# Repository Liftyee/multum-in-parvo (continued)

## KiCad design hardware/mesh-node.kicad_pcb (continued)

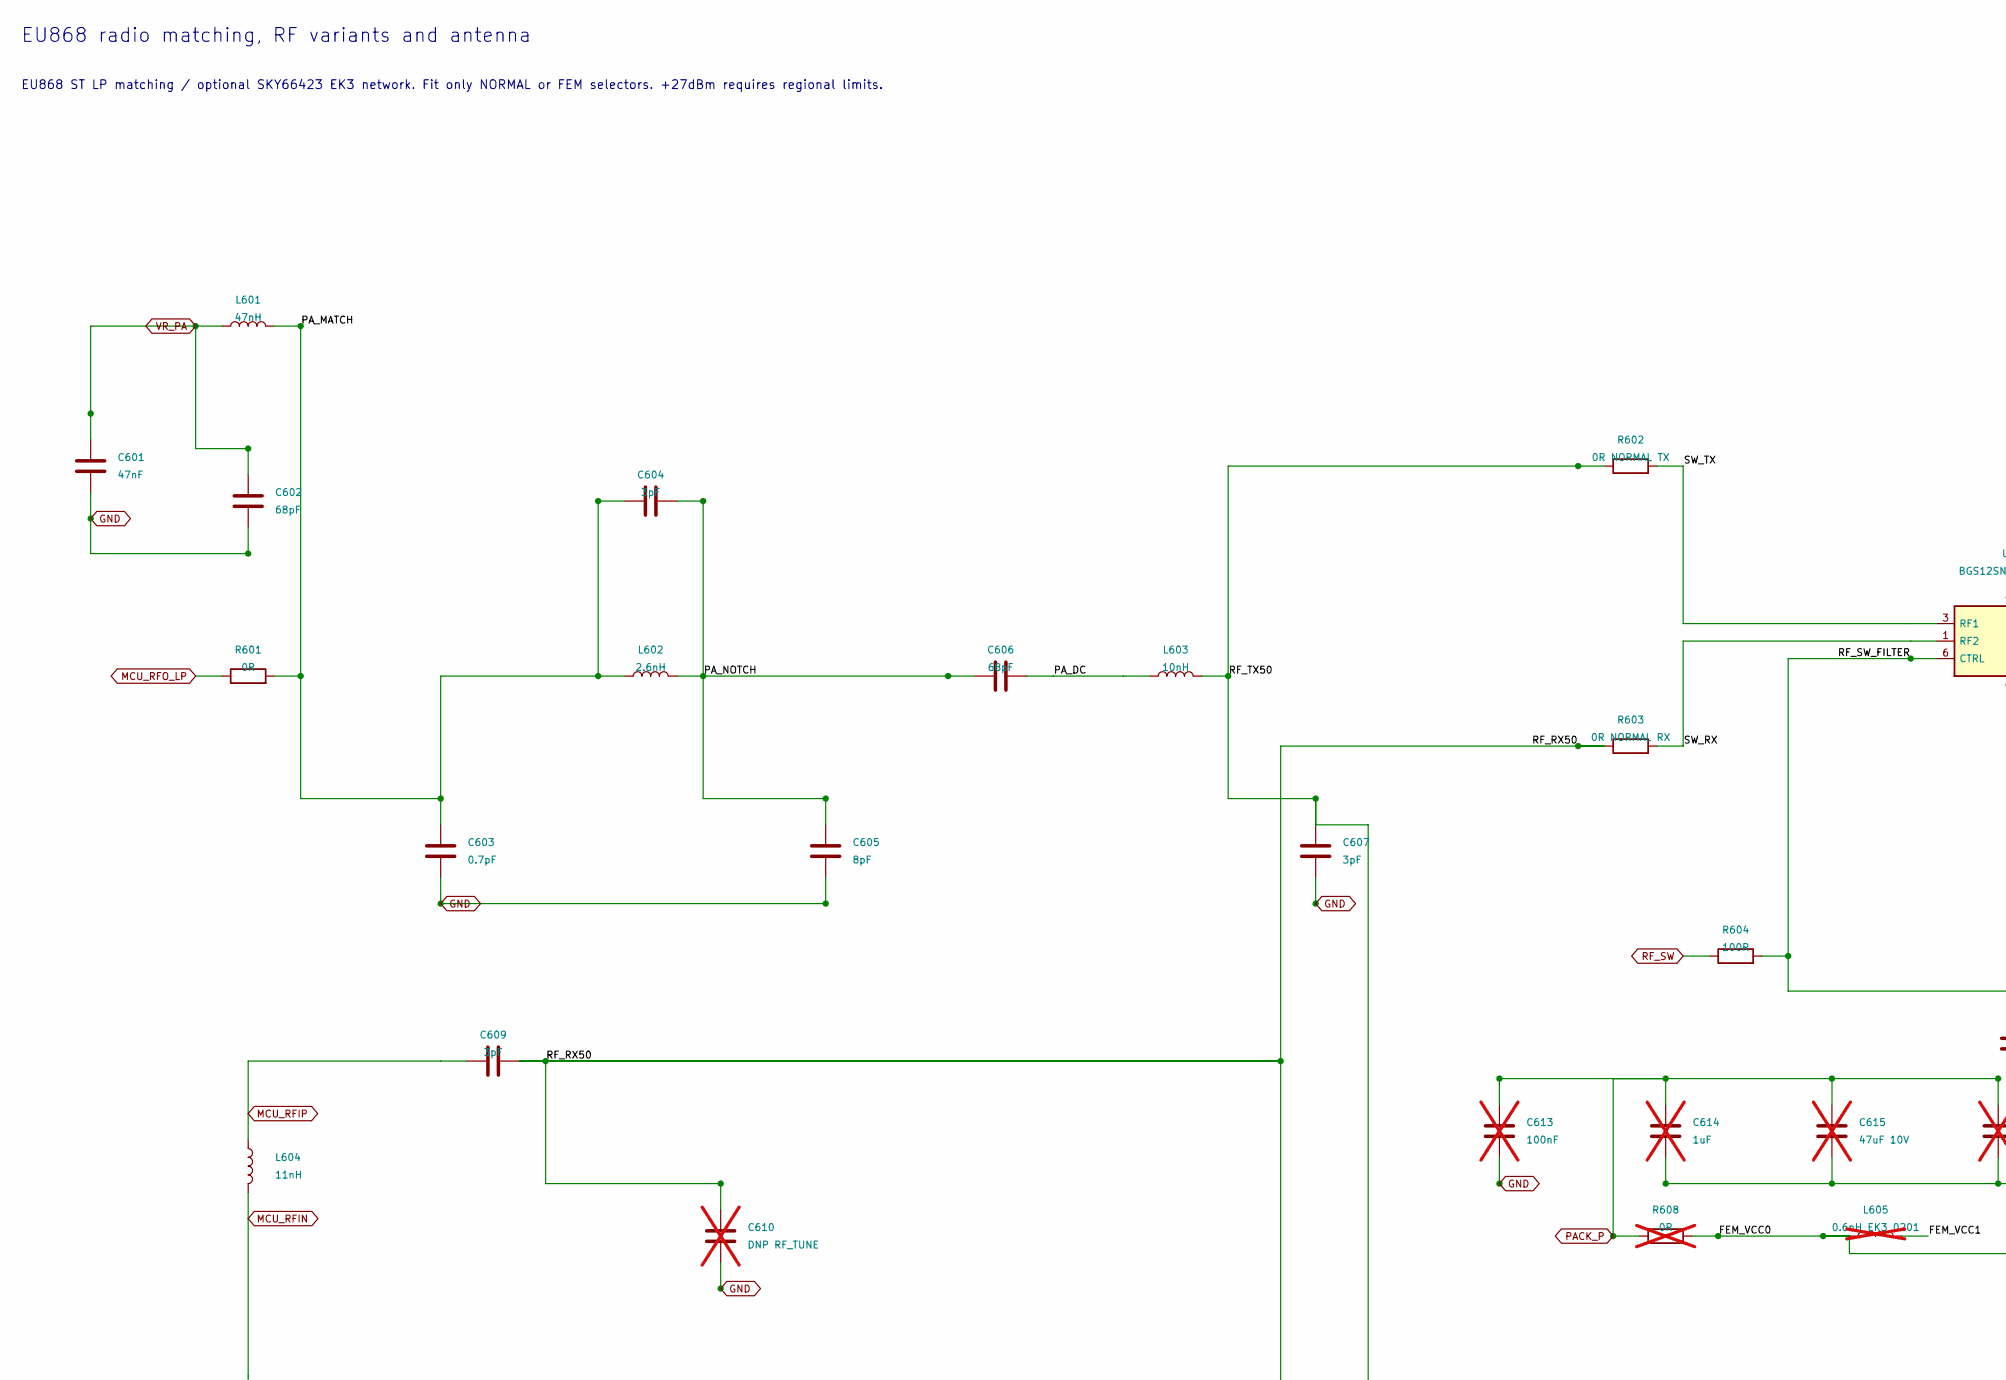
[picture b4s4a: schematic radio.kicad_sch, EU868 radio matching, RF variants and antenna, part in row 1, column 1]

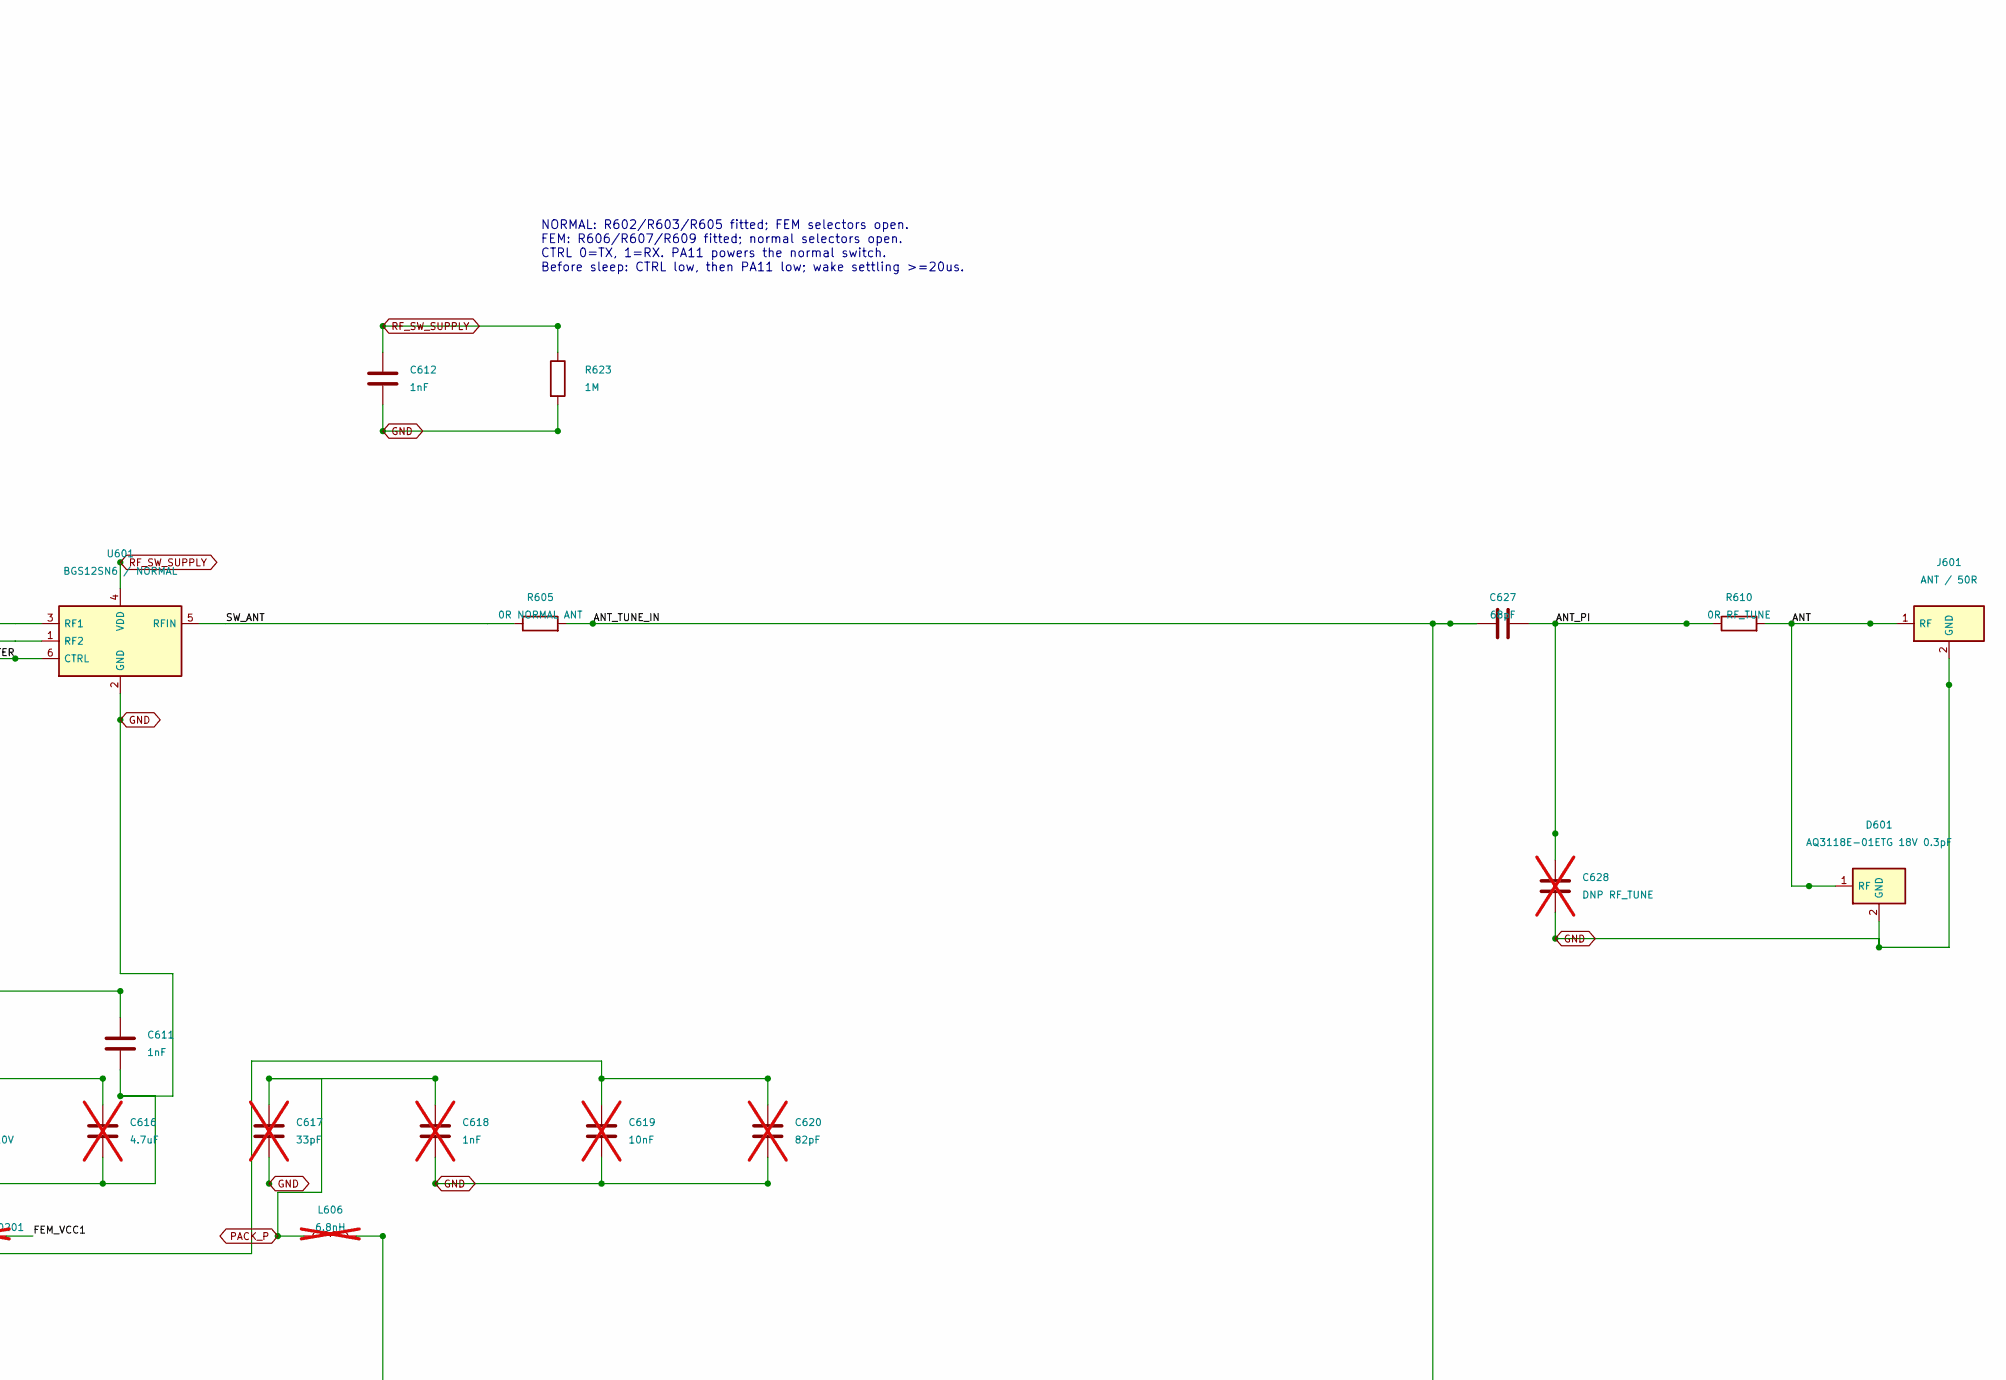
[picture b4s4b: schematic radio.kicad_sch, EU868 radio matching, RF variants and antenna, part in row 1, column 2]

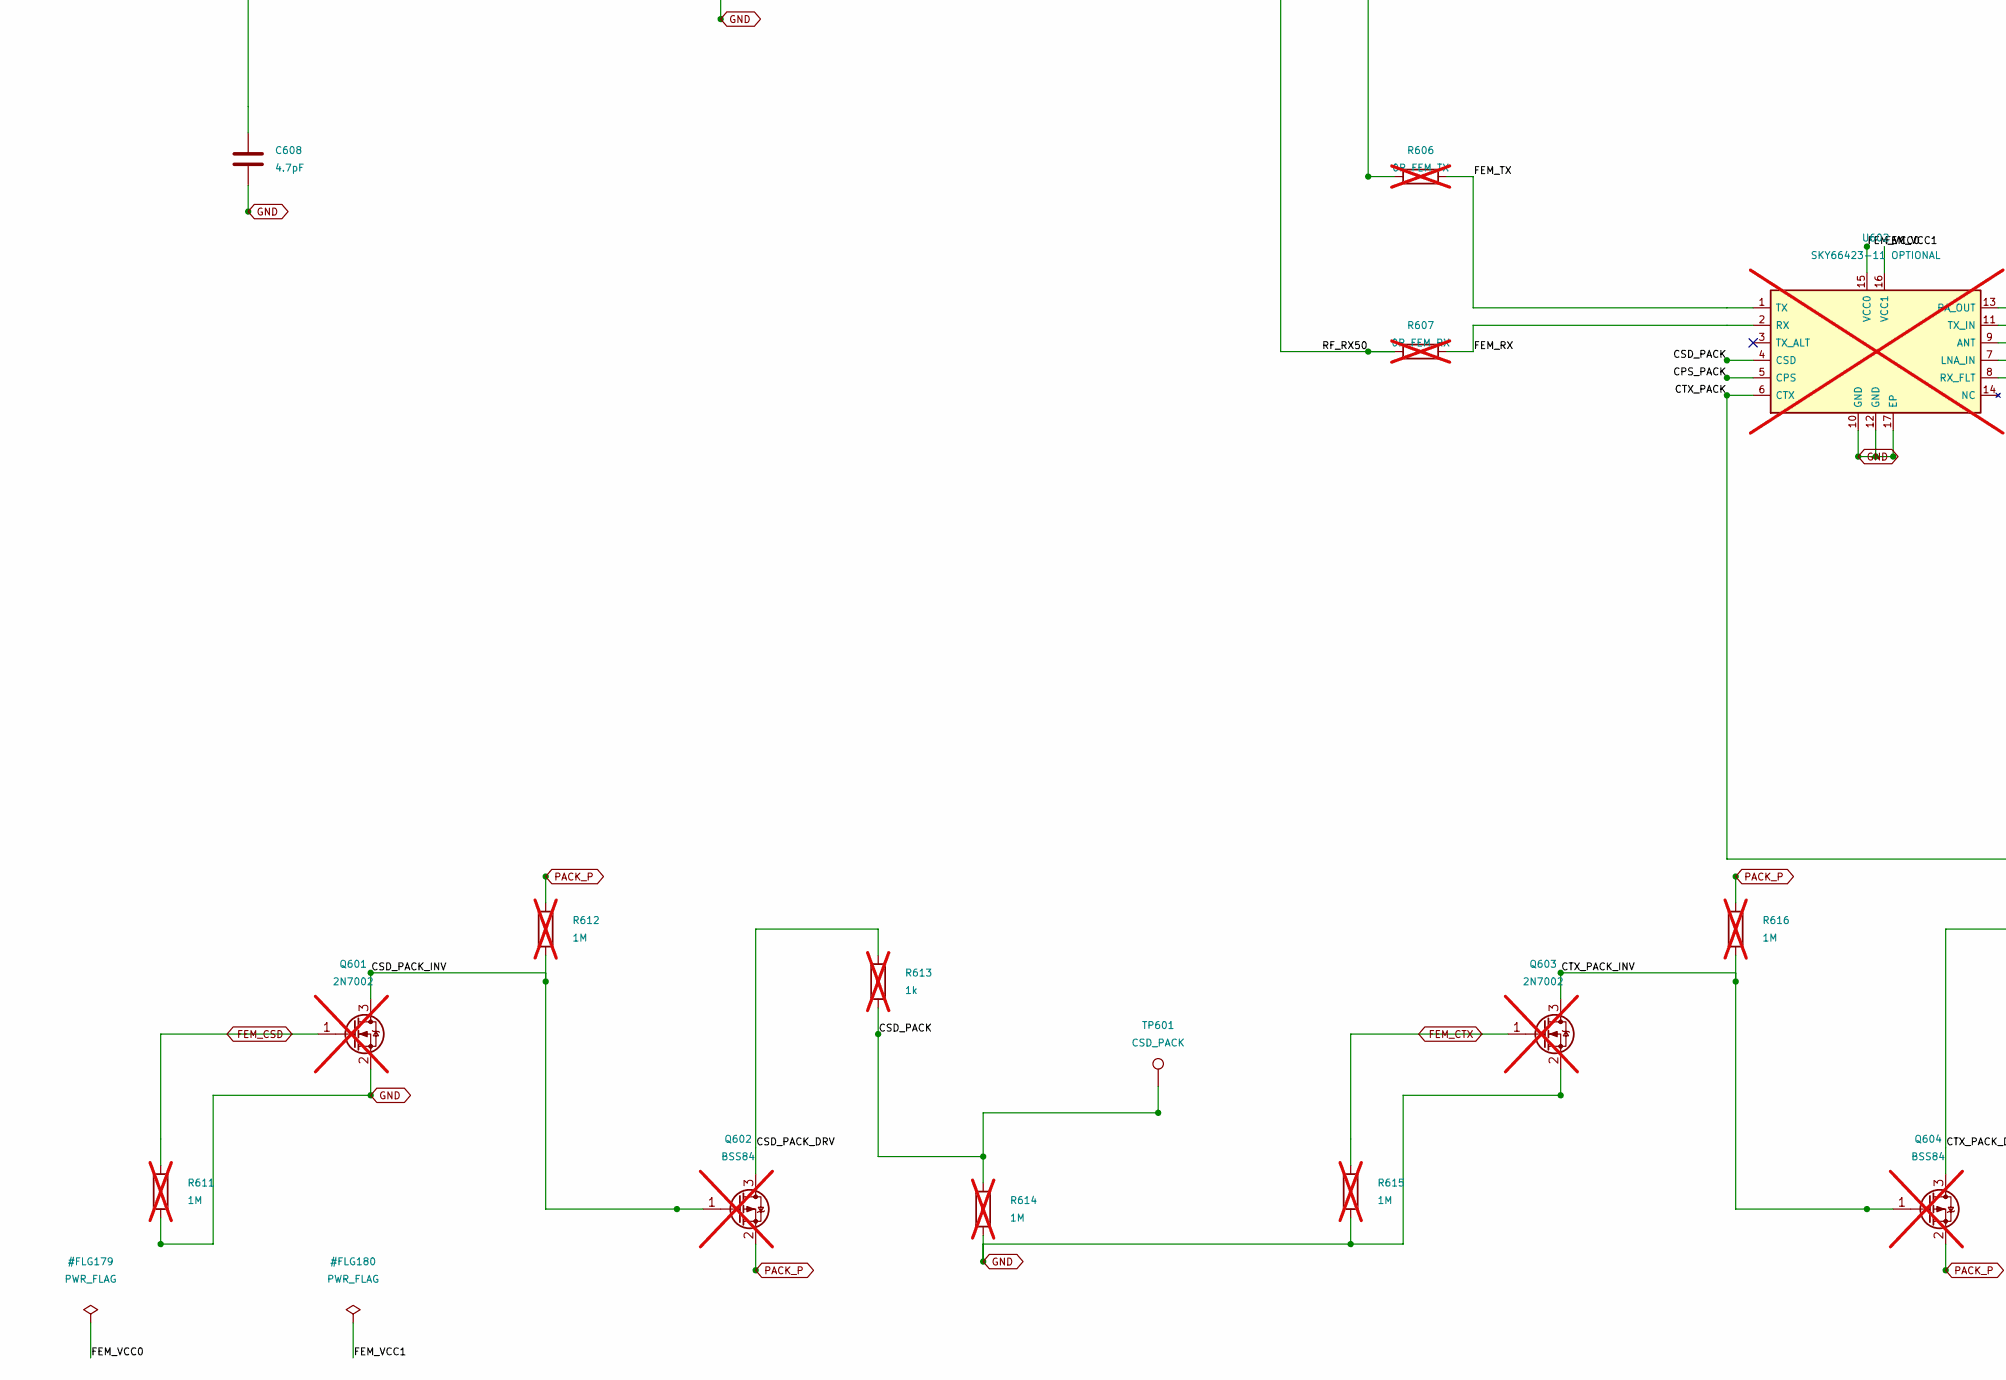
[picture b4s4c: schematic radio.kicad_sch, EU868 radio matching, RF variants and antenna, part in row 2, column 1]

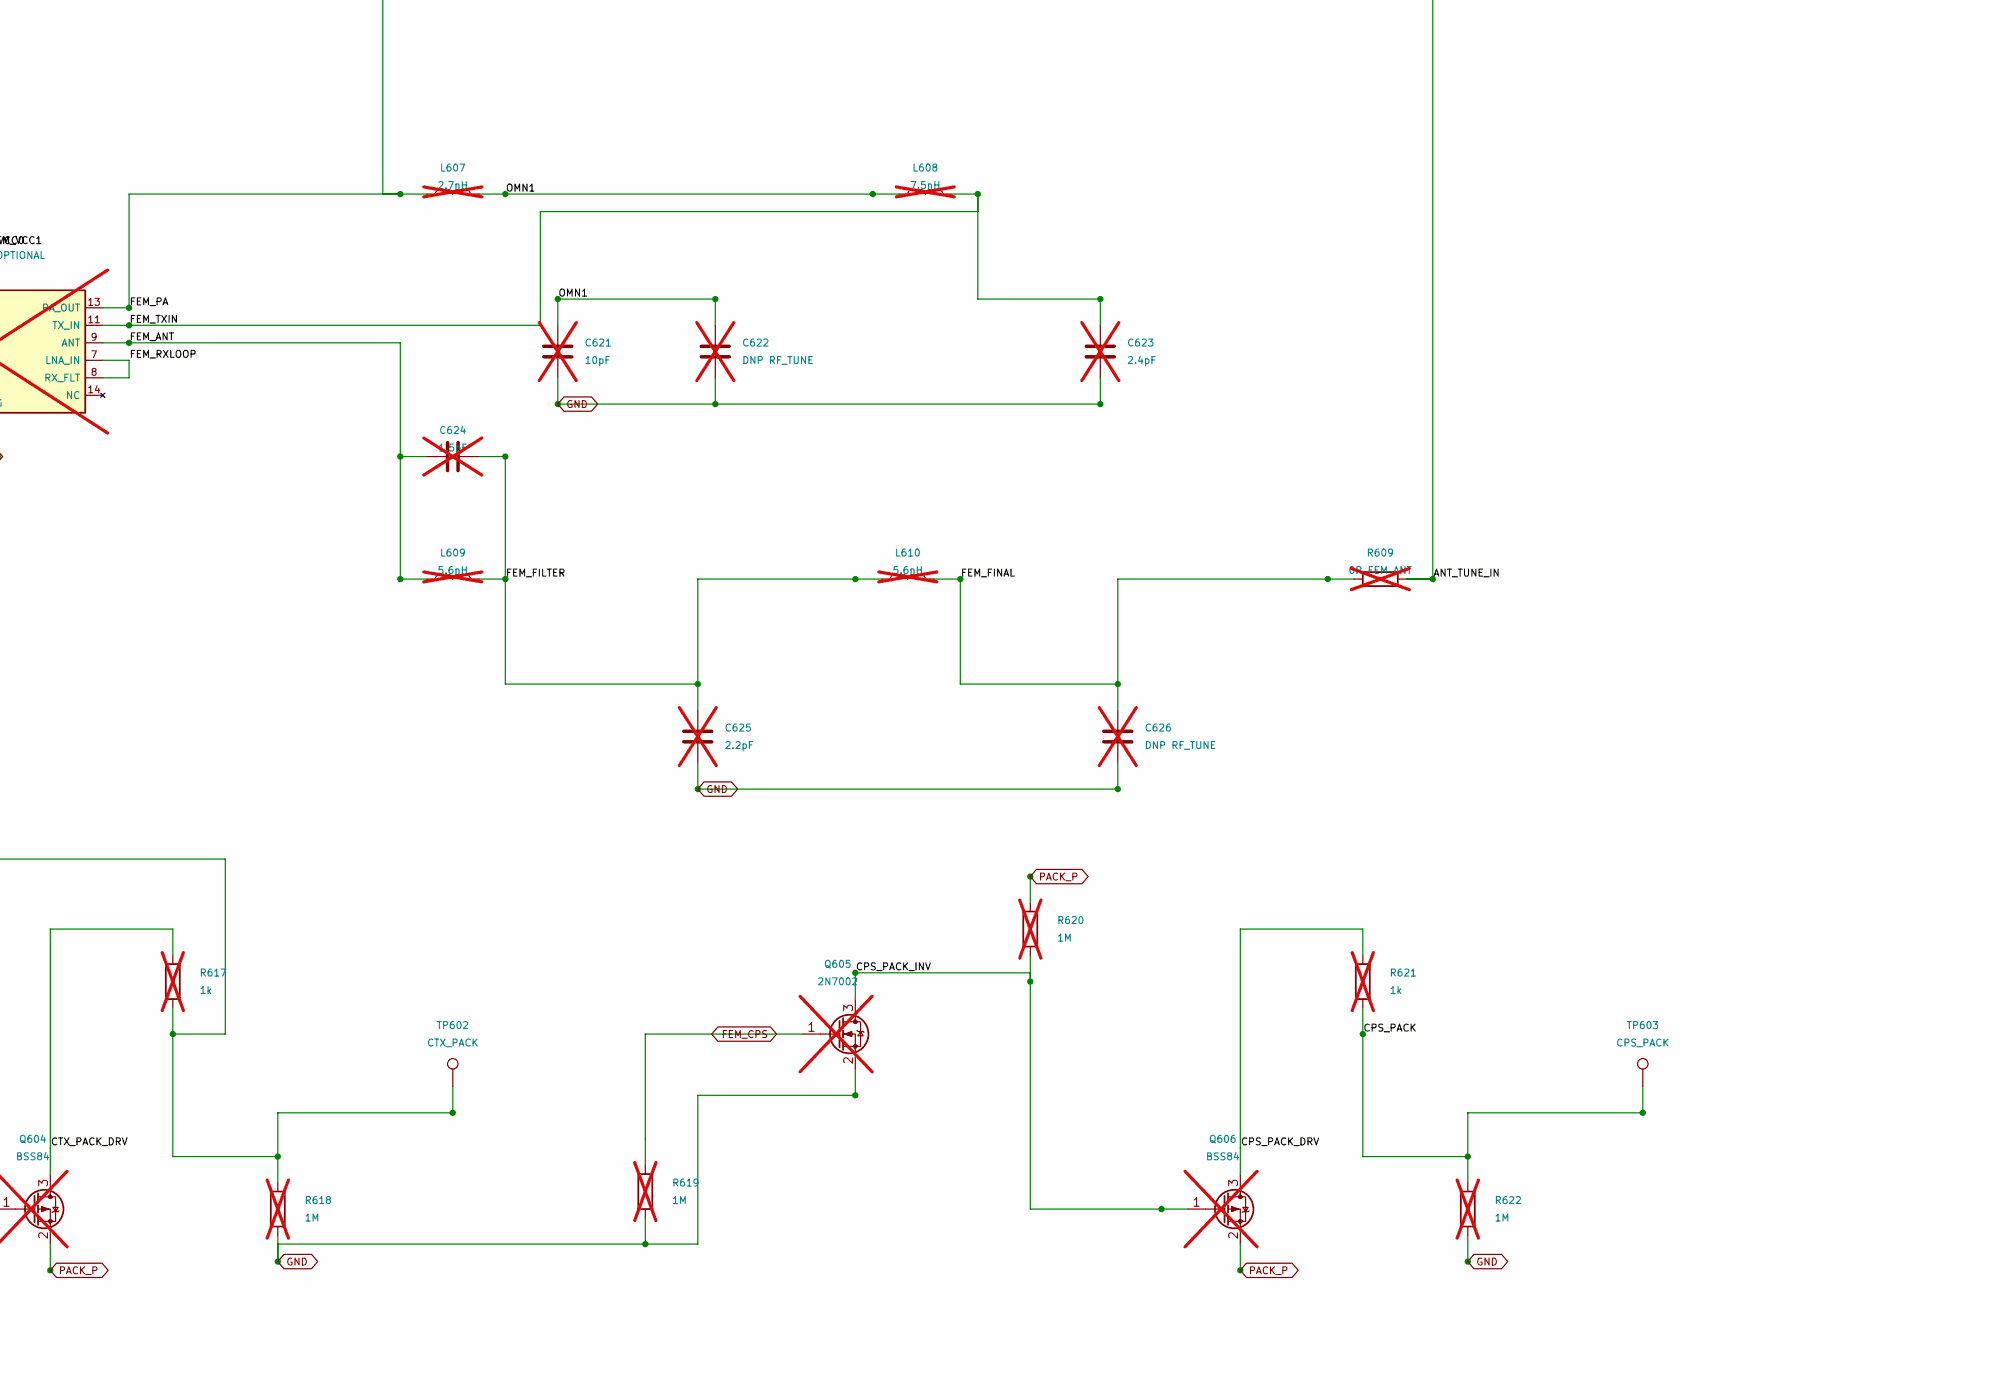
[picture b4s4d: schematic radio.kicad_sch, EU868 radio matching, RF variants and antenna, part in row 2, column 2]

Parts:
C601: 47nF; C0402; MPN 47nF
C602, C606, C627: 68pF; C0402; MPN 68pF
C603: 0.7pF; C0402; MPN 0.7pF
C604, C607, C609: 3pF; C0402; MPN 3pF
C605: 8pF; C0402; MPN 8pF
C608: 4.7pF; C0402; MPN 4.7pF
C610, C622, C626, C628: DNP RF_TUNE; C0402; MPN DNP RF_TUNE; not fitted
C611, C612: 1nF; C0402; MPN 1nF
C613: 100nF; C0402; MPN 100nF; not fitted
C614: 1uF; C0402; MPN 1uF; not fitted
C615: 47uF 10V; C0805; MPN 47uF 10V; not fitted
C616: 4.7uF; C0402; MPN 4.7uF; not fitted
C617: 33pF; C0402; MPN 33pF; not fitted
C618: 1nF; C0402; MPN 1nF; not fitted
C619: 10nF; C0402; MPN 10nF; not fitted
C620: 82pF; C0402; MPN 82pF; not fitted
C621: 10pF; C0402; MPN 10pF; not fitted
C623: 2.4pF; C0402; MPN 2.4pF; not fitted
C624: 1.5pF; C0402; MPN 1.5pF; not fitted
C625: 2.2pF; C0402; MPN 2.2pF; not fitted
D601: AQ3118E-01ETG 18V 0.3pF; ESD0402; MPN AQ3118E-01ETG
J601: ANT / 50R; UFL; MPN U.FL-R-SMT-1(10)
L601: 47nH; L0402; MPN 47nH
L602: 2.6nH; L0402; MPN 2.6nH
L603: 10nH; L0402; MPN 10nH
L604: 11nH; L0402; MPN 11nH
L605: 0.6nH EK3 0201; L0201; MPN LQP03TN0N6B02D; not fitted
L606: 6.8nH; L0402; MPN 6.8nH; not fitted
L607: 2.7nH; L0402; MPN 2.7nH; not fitted
L608: 7.5nH; L0402; MPN 7.5nH; not fitted
L609, L610: 5.6nH; L0402; MPN 5.6nH; not fitted
Q601, Q603, Q605: 2N7002; SOT23; MPN 2N7002; not fitted
Q602, Q604, Q606: BSS84; SOT23; MPN BSS84; not fitted
R601: 0R; R0402; MPN 0R
R602: 0R NORMAL TX; R0402; MPN 0R NORMAL TX
R603: 0R NORMAL RX; R0402; MPN 0R NORMAL RX
R604: 100R; R0603; MPN 100R
R605: 0R NORMAL ANT; R0402; MPN 0R NORMAL ANT
R606: 0R FEM TX; R0402; MPN 0R FEM TX; not fitted
R607: 0R FEM RX; R0402; MPN 0R FEM RX; not fitted
R608: 0R; R0805; MPN 0R; not fitted
R609: 0R FEM ANT; R0402; MPN 0R FEM ANT; not fitted
R610: 0R RF_TUNE; R0402; MPN 0R RF_TUNE
R611, R612, R614, R615, R616, R618, R619, R620, R622: 1M; R0603; MPN 1M; not fitted
R613, R617, R621: 1k; R0603; MPN 1k; not fitted
R623: 1M; R0603; MPN 1M
TP601: CSD_PACK; TestPad; MPN CSD_PACK
TP602: CTX_PACK; TestPad; MPN CTX_PACK
TP603: CPS_PACK; TestPad; MPN CPS_PACK
U601: BGS12SN6 / NORMAL; BGS12SN6; MPN BGS12SN6 / NORMAL
U602: SKY66423-11 OPTIONAL; SKY66423_MCM16; MPN SKY66423-11 OPTIONAL; not fitted

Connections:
/EU868 radio matching, RF variants and antenna/ANT: D601.1 (RF), J601.1 (RF), R610.2
/EU868 radio matching, RF variants and antenna/ANT_PI: C627.2, C628.1, R610.1
/EU868 radio matching, RF variants and antenna/ANT_TUNE_IN: C627.1, R605.2, R609.2
/EU868 radio matching, RF variants and antenna/CPS_PACK: R621.2, R622.1, TP603.1, U602.5 (CPS)
/EU868 radio matching, RF variants and antenna/CPS_PACK_DRV: Q606.3 (D), R621.1
/EU868 radio matching, RF variants and antenna/CPS_PACK_INV: Q605.3 (D), Q606.1 (G), R620.2
/EU868 radio matching, RF variants and antenna/CSD_PACK: R613.2, R614.1, TP601.1, U602.4 (CSD)
/EU868 radio matching, RF variants and antenna/CSD_PACK_DRV: Q602.3 (D), R613.1
/EU868 radio matching, RF variants and antenna/CSD_PACK_INV: Q601.3 (D), Q602.1 (G), R612.2
/EU868 radio matching, RF variants and antenna/CTX_PACK: R617.2, R618.1, TP602.1, U602.6 (CTX)
/EU868 radio matching, RF variants and antenna/CTX_PACK_DRV: Q604.3 (D), R617.1
/EU868 radio matching, RF variants and antenna/CTX_PACK_INV: Q603.3 (D), Q604.1 (G), R616.2
/EU868 radio matching, RF variants and antenna/FEM_ANT: C624.1, L609.1, U602.9 (ANT)
/EU868 radio matching, RF variants and antenna/FEM_FILTER: C624.2, C625.1, L609.2, L610.1
/EU868 radio matching, RF variants and antenna/FEM_FINAL: C626.1, L610.2, R609.1
/EU868 radio matching, RF variants and antenna/FEM_PA: L606.2, L607.1, U602.13 (PA_OUT)
/EU868 radio matching, RF variants and antenna/FEM_RX: R607.2, U602.2 (RX)
/EU868 radio matching, RF variants and antenna/FEM_RXLOOP: U602.7 (LNA_IN), U602.8 (RX_FLT)
/EU868 radio matching, RF variants and antenna/FEM_TX: R606.2, U602.1 (TX)
/EU868 radio matching, RF variants and antenna/FEM_TXIN: C623.1, L608.2, U602.11 (TX_IN)
/EU868 radio matching, RF variants and antenna/FEM_VCC0: C619.1, C620.1, L605.1, R608.2, U602.15 (VCC0)
/EU868 radio matching, RF variants and antenna/FEM_VCC1: L605.2, U602.16 (VCC1)
/EU868 radio matching, RF variants and antenna/OMN1: C621.1, C622.1, L607.2, L608.1
/EU868 radio matching, RF variants and antenna/PA_DC: C606.2, L603.1
/EU868 radio matching, RF variants and antenna/PA_MATCH: C603.1, C604.1, L601.2, L602.1, R601.2
/EU868 radio matching, RF variants and antenna/PA_NOTCH: C604.2, C605.1, C606.1, L602.2
/EU868 radio matching, RF variants and antenna/RF_RX50: C609.2, C610.1, R603.1, R607.1
/EU868 radio matching, RF variants and antenna/RF_SW_FILTER: C611.1, R604.2, U601.6 (CTRL)
/EU868 radio matching, RF variants and antenna/RF_TX50: C607.1, L603.2, R602.1, R606.1
/EU868 radio matching, RF variants and antenna/SW_ANT: R605.1, U601.5 (RFIN)
/EU868 radio matching, RF variants and antenna/SW_RX: R603.2, U601.1 (RF2)
/EU868 radio matching, RF variants and antenna/SW_TX: R602.2, U601.3 (RF1)
FEM_CPS: Q605.1 (G), R619.1; also elsewhere on the board
FEM_CSD: Q601.1 (G), R611.1; also elsewhere on the board
FEM_CTX: Q603.1 (G), R615.1; also elsewhere on the board
GND: C601.2, C602.2, C603.2, C605.2, C607.2, C608.2, C610.2, C611.2, C612.2, C613.2, C614.2, C615.2, C616.2, C617.2, C618.2, C619.2, C620.2, C621.2, C622.2, C623.2, C625.2, C626.2, C628.2, D601.2 (GND), J601.2 (GND), Q601.2 (S), Q603.2 (S), Q605.2 (S), R611.2, R614.2, R615.2, R618.2, R619.2, R622.2, R623.2, U601.2 (GND), U602.10 (GND), U602.12 (GND), U602.17 (EP); also elsewhere on the board
MCU_RFIN: C608.1, L604.2; also elsewhere on the board
MCU_RFIP: C609.1, L604.1; also elsewhere on the board
MCU_RFO_LP: R601.1; also elsewhere on the board
PACK_P: C613.1, C614.1, C615.1, C616.1, C617.1, C618.1, L606.1, Q602.2 (S), Q604.2 (S), Q606.2 (S), R608.1, R612.1, R616.1, R620.1; also elsewhere on the board
RF_SW: R604.1; also elsewhere on the board
RF_SW_SUPPLY: C612.1, R623.1, U601.4 (VDD); also elsewhere on the board
VR_PA: C601.1, C602.1, L601.1; also elsewhere on the board

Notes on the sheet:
EU868 radio matching, RF variants and antenna
EU868 ST LP matching / optional SKY66423 EK3 network. Fit only NORMAL or FEM selectors. +27dBm requires regional limits.
NORMAL: R602/R603/R605 fitted; FEM selectors open. FEM: R606/R607/R609 fitted; normal selectors open. CTRL 0=TX, 1=RX. PA11 powers the normal switch. Before sleep: CTRL low, then PA11 low; wake settling >=20us.

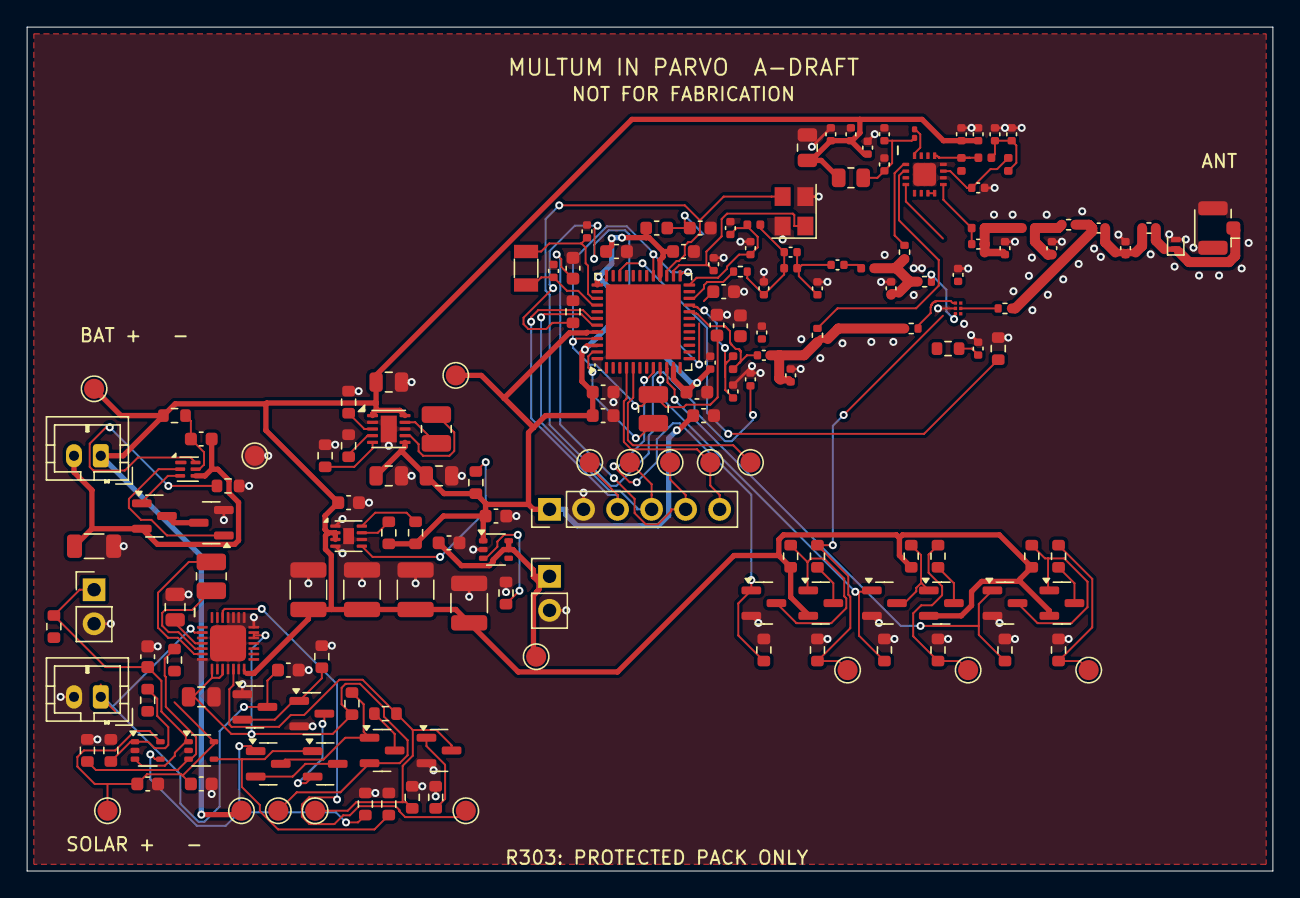
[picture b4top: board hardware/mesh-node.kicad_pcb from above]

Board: 2 copper layers, 93.0 x 63.0 mm, 172 parts (0 on the bottom side), 91 nets.
